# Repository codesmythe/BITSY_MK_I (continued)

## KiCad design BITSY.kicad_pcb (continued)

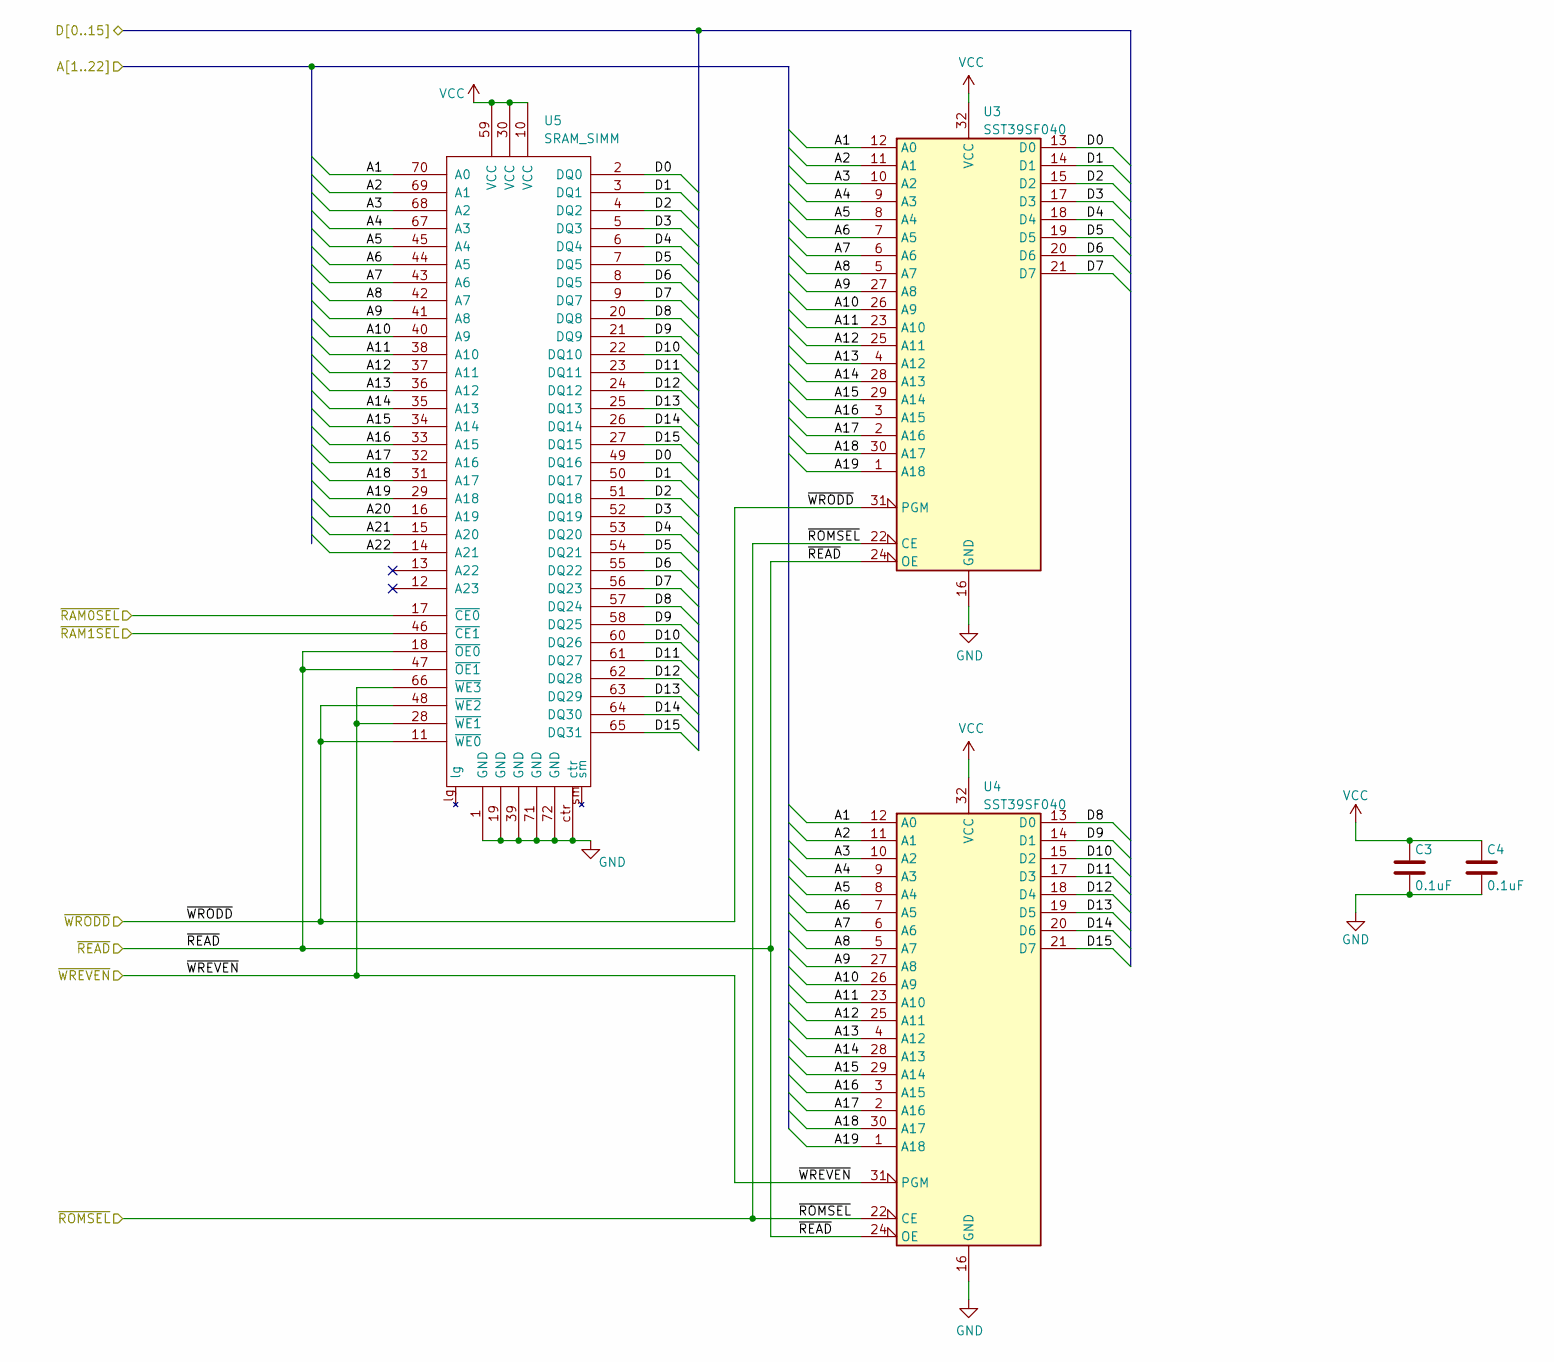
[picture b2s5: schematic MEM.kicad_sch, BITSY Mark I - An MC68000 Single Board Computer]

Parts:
C3, C4: 0.1uF; C_Rect_L7.0mm_W2.0mm_P5.00mm; PartNum00 594-K104K15X7RF5TH5
U3, U4: SST39SF040; PLCC-32_THT-Socket; PartNum00 579-39SF040554CNHET
U5: SRAM_SIMM; DRAM-72-2021; PartNum00 571-5822021-4

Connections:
/A1: U3.12 (A0), U4.12 (A0), U5.70 (A0); also elsewhere on the board
/A2: U3.11 (A1), U4.11 (A1), U5.69 (A1); also elsewhere on the board
/A3: U3.10 (A2), U4.10 (A2), U5.68 (A2); also elsewhere on the board
/A4: U3.9 (A3), U4.9 (A3), U5.67 (A3); also elsewhere on the board
/A5: U3.8 (A4), U4.8 (A4), U5.45 (A4); also elsewhere on the board
/A6: U3.7 (A5), U4.7 (A5), U5.44 (A5); also elsewhere on the board
/A7: U3.6 (A6), U4.6 (A6), U5.43 (A6); also elsewhere on the board
/A8: U3.5 (A7), U4.5 (A7), U5.42 (A7); also elsewhere on the board
/A9: U3.27 (A8), U4.27 (A8), U5.41 (A8); also elsewhere on the board
/A10: U3.26 (A9), U4.26 (A9), U5.40 (A9); also elsewhere on the board
/A11: U3.23 (A10), U4.23 (A10), U5.38 (A10); also elsewhere on the board
/A12: U3.25 (A11), U4.25 (A11), U5.37 (A11); also elsewhere on the board
/A13: U3.4 (A12), U4.4 (A12), U5.36 (A12); also elsewhere on the board
/A14: U3.28 (A13), U4.28 (A13), U5.35 (A13); also elsewhere on the board
/A15: U3.29 (A14), U4.29 (A14), U5.34 (A14); also elsewhere on the board
/A16: U3.3 (A15), U4.3 (A15), U5.33 (A15); also elsewhere on the board
/A17: U3.2 (A16), U4.2 (A16), U5.32 (A16); also elsewhere on the board
/A18: U3.30 (A17), U4.30 (A17), U5.31 (A17); also elsewhere on the board
/A19: U3.1 (A18), U4.1 (A18), U5.29 (A18); also elsewhere on the board
/A20: U5.16 (A19); also elsewhere on the board
/A21: U5.15 (A20); also elsewhere on the board
/A22: U5.14 (A21); also elsewhere on the board
/D0: U3.13 (D0), U5.2 (DQ0), U5.49 (DQ16); also elsewhere on the board
/D1: U3.14 (D1), U5.3 (DQ1), U5.50 (DQ17); also elsewhere on the board
/D2: U3.15 (D2), U5.4 (DQ2), U5.51 (DQ18); also elsewhere on the board
/D3: U3.17 (D3), U5.5 (DQ3), U5.52 (DQ19); also elsewhere on the board
/D4: U3.18 (D4), U5.6 (DQ4), U5.53 (DQ20); also elsewhere on the board
/D5: U3.19 (D5), U5.7 (DQ5), U5.54 (DQ21); also elsewhere on the board
/D6: U3.20 (D6), U5.8 (DQ5), U5.55 (DQ22); also elsewhere on the board
/D7: U3.21 (D7), U5.9 (DQ7), U5.56 (DQ23); also elsewhere on the board
/D8: U4.13 (D0), U5.20 (DQ8), U5.57 (DQ24); also elsewhere on the board
/D9: U4.14 (D1), U5.21 (DQ9), U5.58 (DQ25); also elsewhere on the board
/D10: U4.15 (D2), U5.22 (DQ10), U5.60 (DQ26); also elsewhere on the board
/D11: U4.17 (D3), U5.23 (DQ11), U5.61 (DQ27); also elsewhere on the board
/D12: U4.18 (D4), U5.24 (DQ12), U5.62 (DQ28); also elsewhere on the board
/D13: U4.19 (D5), U5.25 (DQ13), U5.63 (DQ29); also elsewhere on the board
/D14: U4.20 (D6), U5.26 (DQ14), U5.64 (DQ30); also elsewhere on the board
/D15: U4.21 (D7), U5.27 (DQ15), U5.65 (DQ31); also elsewhere on the board
/~RAM0CS: U5.17 (~CE0); also elsewhere on the board
/~RAM1CS: U5.46 (~CE1); also elsewhere on the board
/~READ: U3.24 (OE), U4.24 (OE), U5.18 (~OE0), U5.47 (~OE1); also elsewhere on the board
/~ROMCS: U3.22 (CE), U4.22 (CE); also elsewhere on the board
/~WREVEN: U4.31 (PGM), U5.28 (~WE1), U5.66 (~WE3); also elsewhere on the board
/~WRODD: U3.31 (PGM), U5.11 (~WE0), U5.48 (~WE2); also elsewhere on the board
GND: C3.2, C4.2, U3.16 (GND), U4.16 (GND), U5.1 (GND), U5.19 (GND), U5.39 (GND), U5.71 (GND), U5.72 (GND), U5.ctr; also elsewhere on the board
VCC: C3.1, C4.1, U3.32 (VCC), U4.32 (VCC), U5.10 (VCC), U5.30 (VCC), U5.59 (VCC); also elsewhere on the board

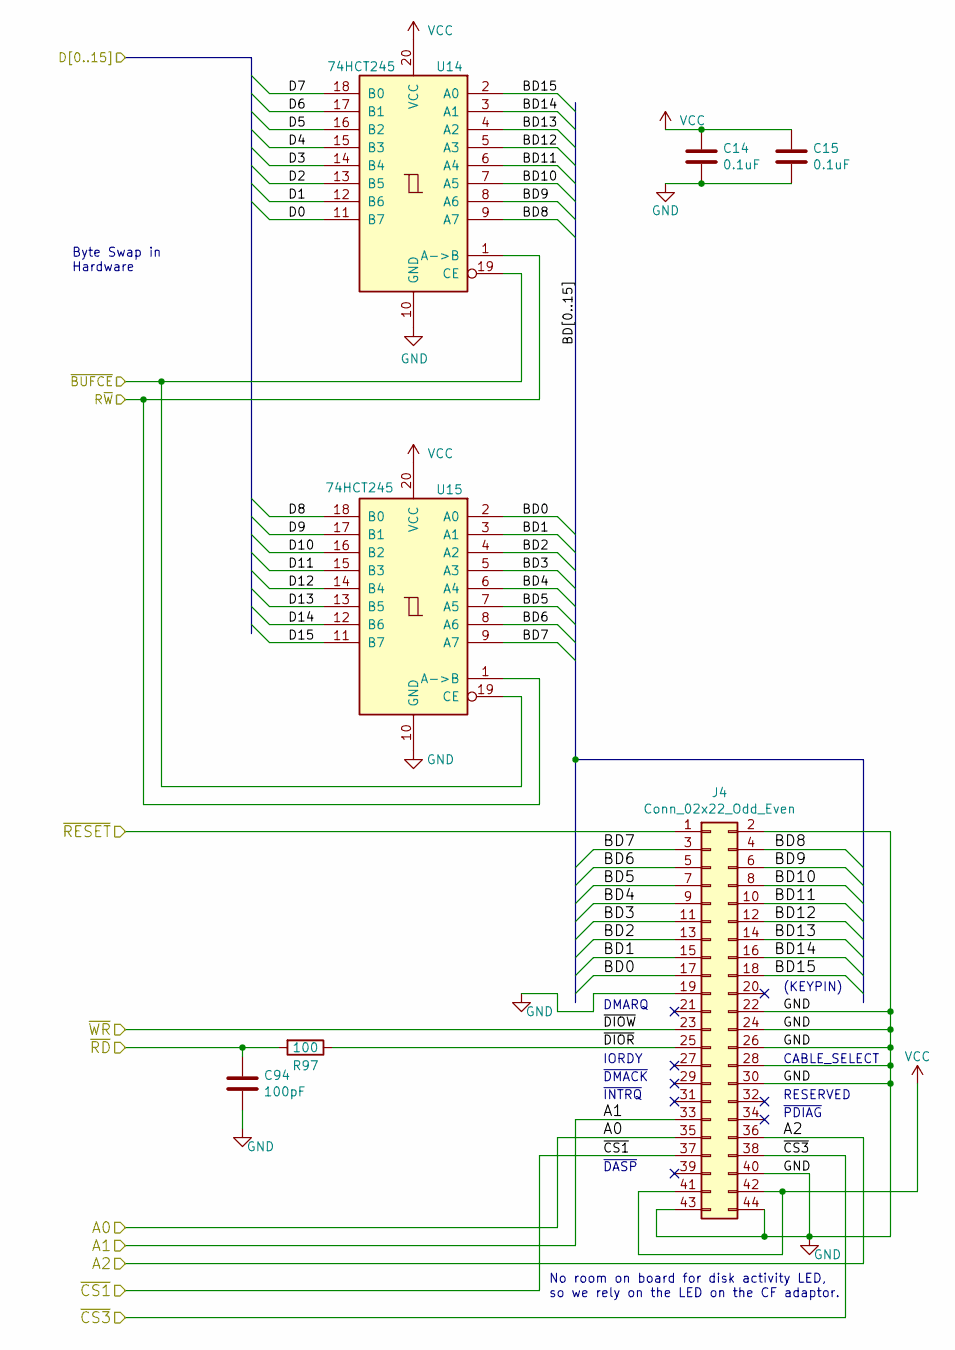
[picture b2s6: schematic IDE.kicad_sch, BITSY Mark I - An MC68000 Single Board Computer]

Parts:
C14, C15: 0.1uF; C_Rect_L7.0mm_W2.0mm_P5.00mm; PartNum00 594-K104K15X7RF5TH5
C94: 100pF; C_Rect_L7.0mm_W2.0mm_P5.00mm; PartNum00 594-K101J15C0GF5TH5
J4: Conn_02x22_Odd_Even; PAD_2X22
R97: 100; R_Axial_DIN0207_L6.3mm_D2.5mm_P7.62mm_Horizontal; PartNum00 603-MFR-25FBF52-100R
U14, U15: 74HCT245; DIP-20_W7.62mm_Socket; PartNum00 595-SN74HCT245N

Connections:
/A2: J4.35; also elsewhere on the board
/A3: J4.33; also elsewhere on the board
/A4: J4.36; also elsewhere on the board
/D0: U14.11 (B7); also elsewhere on the board
/D1: U14.12 (B6); also elsewhere on the board
/D2: U14.13 (B5); also elsewhere on the board
/D3: U14.14 (B4); also elsewhere on the board
/D4: U14.15 (B3); also elsewhere on the board
/D5: U14.16 (B2); also elsewhere on the board
/D6: U14.17 (B1); also elsewhere on the board
/D7: U14.18 (B0); also elsewhere on the board
/D8: U15.18 (B0); also elsewhere on the board
/D9: U15.17 (B1); also elsewhere on the board
/D10: U15.16 (B2); also elsewhere on the board
/D11: U15.15 (B3); also elsewhere on the board
/D12: U15.14 (B4); also elsewhere on the board
/D13: U15.13 (B5); also elsewhere on the board
/D14: U15.12 (B6); also elsewhere on the board
/D15: U15.11 (B7); also elsewhere on the board
/IDE/BD0: J4.17, U15.2 (A0)
/IDE/BD1: J4.15, U15.3 (A1)
/IDE/BD2: J4.13, U15.4 (A2)
/IDE/BD3: J4.11, U15.5 (A3)
/IDE/BD4: J4.9, U15.6 (A4)
/IDE/BD5: J4.7, U15.7 (A5)
/IDE/BD6: J4.5, U15.8 (A6)
/IDE/BD7: J4.3, U15.9 (A7)
/IDE/BD8: J4.4, U14.9 (A7)
/IDE/BD9: J4.6, U14.8 (A6)
/IDE/BD10: J4.8, U14.7 (A5)
/IDE/BD11: J4.10, U14.6 (A4)
/IDE/BD12: J4.12, U14.5 (A3)
/IDE/BD13: J4.14, U14.4 (A2)
/IDE/BD14: J4.16, U14.3 (A1)
/IDE/BD15: J4.18, U14.2 (A0)
/IDE/~DIOR: J4.25, R97.1
/R~W: U14.1 (A->B), U15.1 (A->B); also elsewhere on the board
/~DIOR: C94.1, R97.2; also elsewhere on the board
/~DIOW: J4.23; also elsewhere on the board
/~ICECS: U14.19 (CE), U15.19 (CE); also elsewhere on the board
/~IDECS1: J4.37; also elsewhere on the board
/~IDECS3: J4.38; also elsewhere on the board
/~RESET: J4.1; also elsewhere on the board
GND: C14.2, C15.2, C94.2, J4.2, J4.19, J4.22, J4.24, J4.26, J4.28, J4.30, J4.40, J4.43, J4.44, U14.10 (GND), U15.10 (GND); also elsewhere on the board
VCC: C14.1, C15.1, J4.41, J4.42, U14.20 (VCC), U15.20 (VCC); also elsewhere on the board

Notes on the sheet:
RESERVED
~{INTRQ}
No room on board for disk activity LED, so we rely on the LED on the CF adaptor.
Byte Swap in Hardware
IORDY
(KEYPIN)
~{PDIAG}
~{DASP}
DMARQ
~{DMACK}
CABLE_SELECT

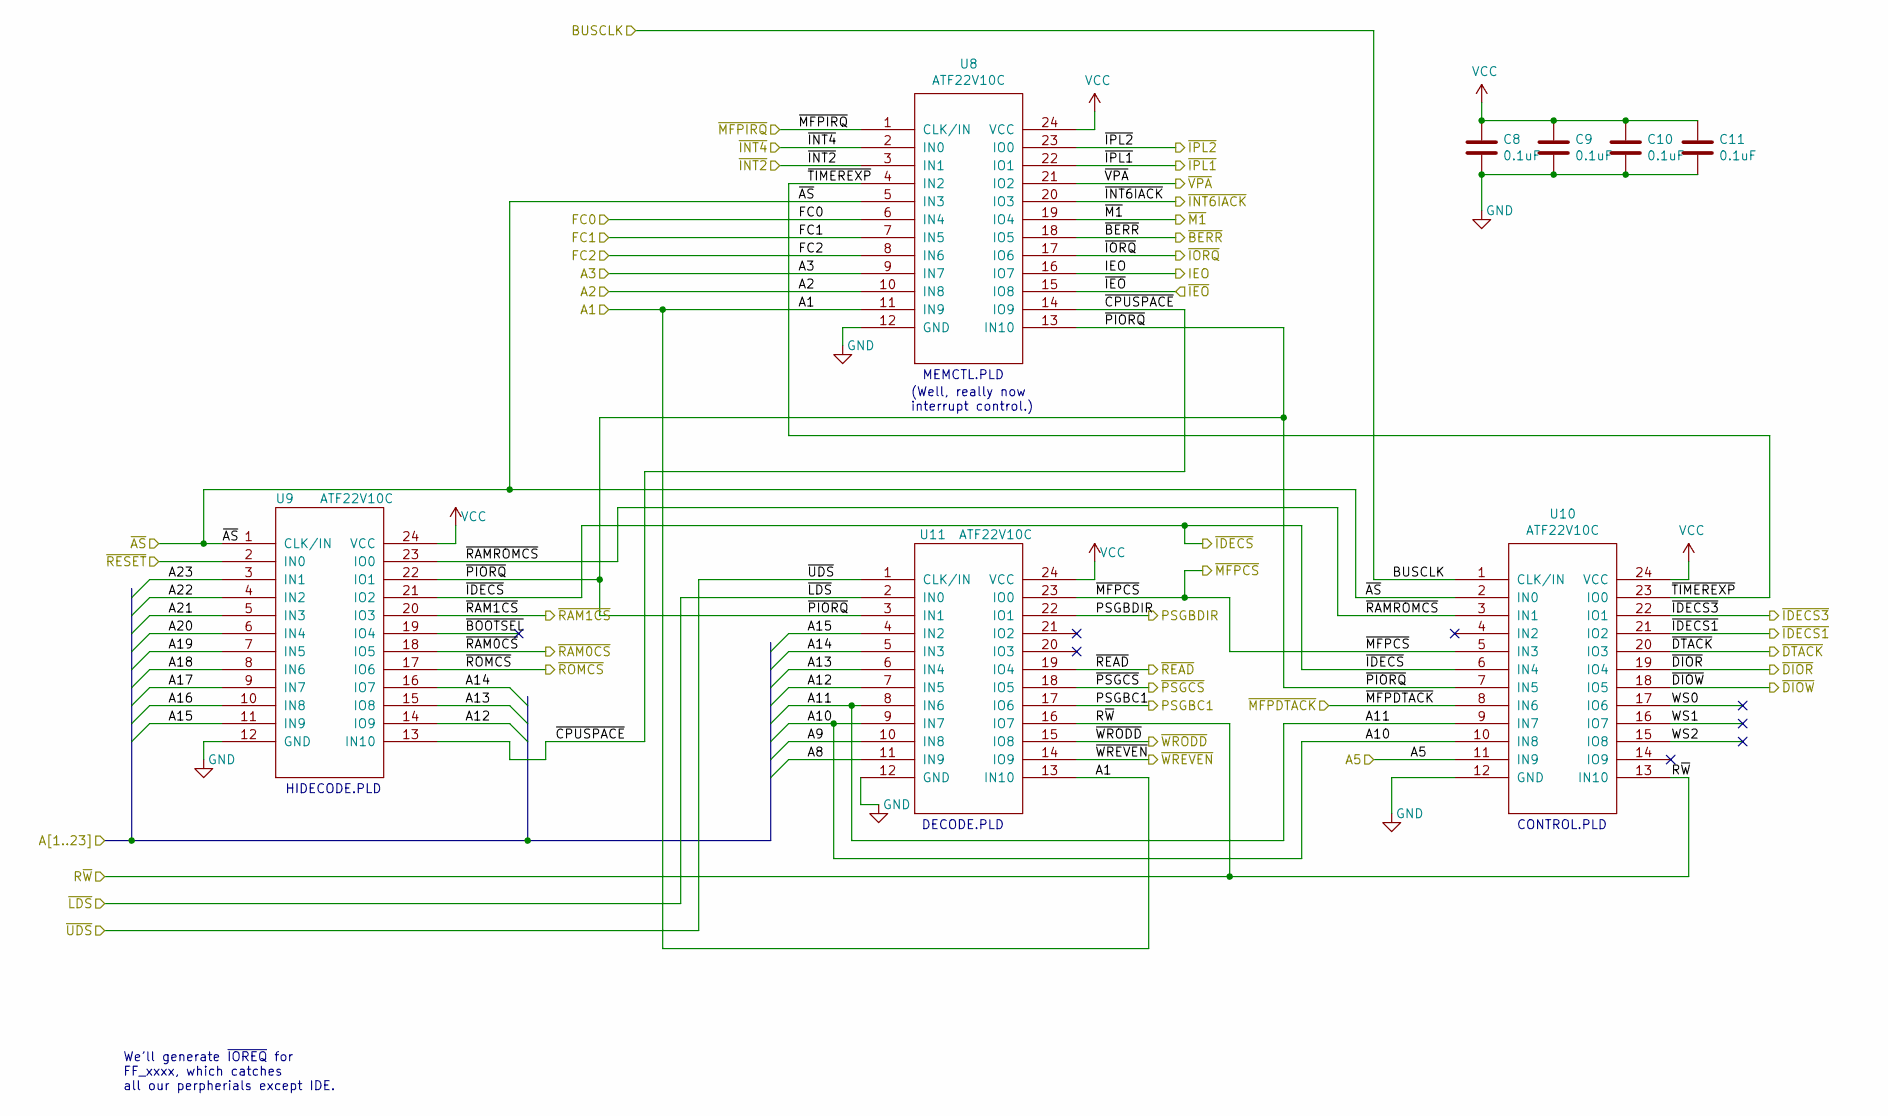
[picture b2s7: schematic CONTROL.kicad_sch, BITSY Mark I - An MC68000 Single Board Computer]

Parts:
C8, C9, C10, C11: 0.1uF; C_Rect_L7.0mm_W2.0mm_P5.00mm; PartNum00 594-K104K15X7RF5TH5
U8, U9, U10, U11: ATF22V10C; DIP-24_W7.62mm_Socket; PartNum00 556-AF22V10C15PU

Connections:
/A1: U8.11 (IN9), U11.13 (IN10); also elsewhere on the board
/A2: U8.10 (IN8); also elsewhere on the board
/A3: U8.9 (IN7); also elsewhere on the board
/A5: U10.11 (IN9); also elsewhere on the board
/A8: U11.11 (IN9); also elsewhere on the board
/A9: U11.10 (IN8); also elsewhere on the board
/A10: U10.10 (IN8), U11.9 (IN7); also elsewhere on the board
/A11: U10.9 (IN7), U11.8 (IN6); also elsewhere on the board
/A12: U9.14 (IO9), U11.7 (IN5); also elsewhere on the board
/A13: U9.15 (IO8), U11.6 (IN4); also elsewhere on the board
/A14: U9.16 (IO7), U11.5 (IN3); also elsewhere on the board
/A15: U9.11 (IN9), U11.4 (IN2); also elsewhere on the board
/A16: U9.10 (IN8); also elsewhere on the board
/A17: U9.9 (IN7); also elsewhere on the board
/A18: U9.8 (IN6); also elsewhere on the board
/A19: U9.7 (IN5); also elsewhere on the board
/A20: U9.6 (IN4); also elsewhere on the board
/A21: U9.5 (IN3); also elsewhere on the board
/A22: U9.4 (IN2); also elsewhere on the board
/A23: U9.3 (IN1); also elsewhere on the board
/BUSCLK: U10.1 (CLK/IN); also elsewhere on the board
/CONTROL/PSGBDIR: U11.22 (IO1); also elsewhere on the board
/CONTROL/WS0: U10.17 (IO6)
/CONTROL/WS1: U10.16 (IO7)
/CONTROL/WS2: U10.15 (IO8)
/CONTROL/~BOOTSEL: U9.19 (IO4)
/CONTROL/~CPUSPACE: U8.14 (IO9), U9.13 (IN10)
/CONTROL/~PIORQ: U8.13 (IN10), U9.22 (IO1), U10.7 (IN5), U11.3 (IN1)
/CONTROL/~RAMROMCS: U9.23 (IO0), U10.3 (IN1)
/CONTROL/~TIMEREXP: U8.4 (IN2), U10.23 (IO0)
/FC0: U8.6 (IN4); also elsewhere on the board
/FC1: U8.7 (IN5); also elsewhere on the board
/FC2: U8.8 (IN6); also elsewhere on the board
/IEO: U8.16 (IO7); also elsewhere on the board
/PSGBC1: U11.17 (IO6); also elsewhere on the board
/R~W: U10.13 (IN10), U11.16 (IO7); also elsewhere on the board
/~AS: U8.5 (IN3), U9.1 (CLK/IN), U10.2 (IN0); also elsewhere on the board
/~BERR: U8.18 (IO5); also elsewhere on the board
/~DIOR: U10.19 (IO4); also elsewhere on the board
/~DIOW: U10.18 (IO5); also elsewhere on the board
/~DTACK: U10.20 (IO3); also elsewhere on the board
/~ICECS: U9.21 (IO2), U10.6 (IN4); also elsewhere on the board
/~IDECS1: U10.21 (IO2); also elsewhere on the board
/~IDECS3: U10.22 (IO1); also elsewhere on the board
/~IEO: U8.15 (IO8); also elsewhere on the board
/~INT2: U8.3 (IN1); also elsewhere on the board
/~INT4: U8.2 (IN0); also elsewhere on the board
/~IORQ: U8.17 (IO6); also elsewhere on the board
/~IPL1: U8.22 (IO1); also elsewhere on the board
/~IPL2: U8.23 (IO0); also elsewhere on the board
/~LDS: U11.2 (IN0); also elsewhere on the board
/~M1: U8.19 (IO4); also elsewhere on the board
/~MFPCS: U10.5 (IN3), U11.23 (IO0); also elsewhere on the board
/~MFPDTACK: U10.8 (IN6); also elsewhere on the board
/~MFPIACK: U8.20 (IO3); also elsewhere on the board
/~MFPIRQ: U8.1 (CLK/IN); also elsewhere on the board
/~PSGCS: U11.18 (IO5); also elsewhere on the board
/~RAM0CS: U9.18 (IO5); also elsewhere on the board
/~RAM1CS: U9.20 (IO3); also elsewhere on the board
/~READ: U11.19 (IO4); also elsewhere on the board
/~RESET: U9.2 (IN0); also elsewhere on the board
/~ROMCS: U9.17 (IO6); also elsewhere on the board
/~UDS: U11.1 (CLK/IN); also elsewhere on the board
/~VPA: U8.21 (IO2); also elsewhere on the board
/~WREVEN: U11.14 (IO9); also elsewhere on the board
/~WRODD: U11.15 (IO8); also elsewhere on the board
GND: C8.2, C9.2, C10.2, C11.2, U8.12 (GND), U9.12 (GND), U10.12 (GND), U11.12 (GND); also elsewhere on the board
VCC: C8.1, C9.1, C10.1, C11.1, U8.24 (VCC), U9.24 (VCC), U10.24 (VCC), U11.24 (VCC); also elsewhere on the board

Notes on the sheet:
HIDECODE.PLD
CONTROL.PLD
MEMCTL.PLD
We’ll generate ~{IOREQ} for FF_xxxx, which catches all our perpherials except IDE.
DECODE.PLD
(Well, really now interrupt control.)

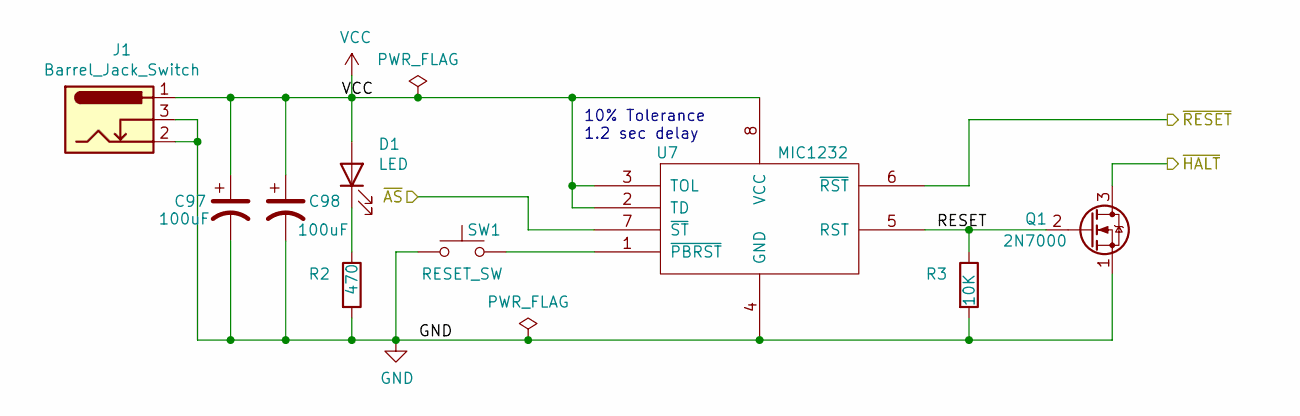
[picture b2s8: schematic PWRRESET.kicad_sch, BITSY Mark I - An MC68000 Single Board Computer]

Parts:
C97, C98: 100uF; CP_Radial_Tantal_D4.5mm_P2.50mm; PartNum00 667-ECA-1CM101I
D1: LED; LED_D5.0mm; PartNum00 859-LTL-307GLC
J1: Barrel_Jack_Switch; BarrelJack_Horizontal; PartNum00 490-PJ-002A
Q1: 2N7000; TO-92_HandSolder; PartNum00 512-2N7000
R2: 470; R_Axial_DIN0207_L6.3mm_D2.5mm_P7.62mm_Horizontal; PartNum00 603-MFR-25FTE52-470R
R3: 10K; R_Axial_DIN0207_L6.3mm_D2.5mm_P7.62mm_Horizontal; PartNum00 603-MFR-25FTE52-10K
SW1: RESET_SW; SW_PUSH_6mm; PartNum00 179-TS026655BK160LCR
U7: MIC1232; DIP-8_W7.62mm_Socket_LongPads; PartNum00 998-MIC1232NY

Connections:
/PWRRESET/RESET: Q1.2 (G), R3.1, U7.5 (RST)
/~AS: U7.7 (~ST); also elsewhere on the board
/~HALT: Q1.3 (D); also elsewhere on the board
/~RESET: U7.6 (~RST); also elsewhere on the board
GND: C97.2, C98.2, J1.2, J1.3, Q1.1 (S), R2.2, R3.2, SW1.1, U7.4 (GND); also elsewhere on the board
unnamed: D1.1 (K), R2.1
unnamed: SW1.2, U7.1 (~PBRST)
VCC: C97.1, C98.1, D1.2 (A), J1.1, U7.2 (TD), U7.3 (TOL), U7.8 (VCC); also elsewhere on the board

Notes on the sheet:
10% Tolerance 1.2 sec delay

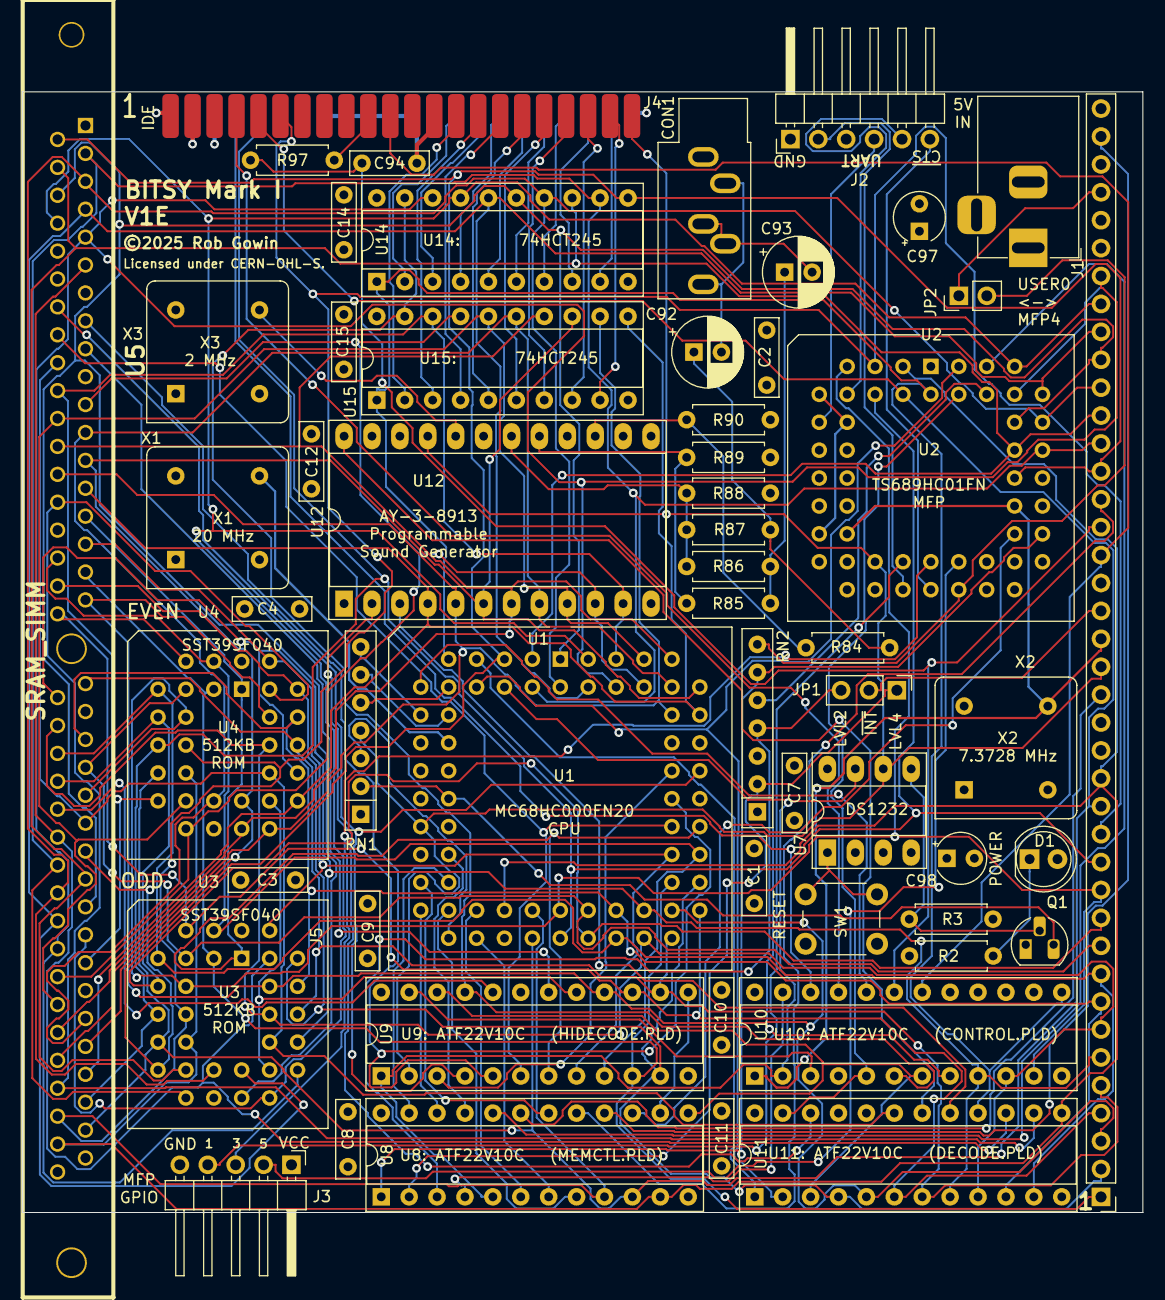
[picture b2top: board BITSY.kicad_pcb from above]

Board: 4 copper layers, 102.0 x 102.0 mm, 56 parts (0 on the bottom side), 128 nets.

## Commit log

2025-06-17 Initial commit.
2025-06-17 Remove interactive BOM link for now.
2025-06-17 Add info about full system.
2025-08-10 Fix issue with interrupt acknowledge.
    Also, add proper support for using 68K interrupt level 2.
2025-08-15 V1C version of BITSY that uses an SRAM SIMM for memory.
    This version sent to JLCPCB on 08/15/2025.
2025-08-16 Add part numbers.
    No board change.
2025-09-11 ~{MREQ} now used for ~{RAM1CS}.
2025-09-11 Use one READ signal, not two.
    Previously, the DECODE GAL generated separate reads for
    even and odd bytes. But this is unnecessary and now there
    is just a single READ signal.
2025-09-11 Add PLD files for 2 MB and 8 MB systems.
2025-09-25 Add two extra SIMM address lines.
2025-10-02 Update version info
2025-10-09 Update part numbers.
2025-10-11 Update documentation.
2025-11-10 Create V1E version.
    Adds extra address line to SIMM for 16 MB support.
2025-11-16 MEMCTL.PLD: INT6IACK should only acknowledge INT6.
    Thanks to Bill Bond for the bug report.
2025-11-19 MEMCTL: Assert INT6IACK only for level 6 interrupts.
    Thanks to Bill Bond for the bug report.
2025-11-20 Add routed PCB for V1E.
2025-11-27 Update docs, ROMs and PLDs for V1E version.
2025-11-27 More doc updates.
2025-11-29 Add 1 MB SRAM SIMM design.
2025-11-29 Update project file.
2025-11-29 Add V1E Gerber file.
